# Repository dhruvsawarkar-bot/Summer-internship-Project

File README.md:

Analog Front-End PCB Design for Cyclic Voltammetry.
This project focuses on the design and development of an Analog Front-End current sensing circuit created for a Cyclic Voltammetry system. Developed during a research internship at the Sixth Sense Lab, IISER Bhopal, this board detects tiny electrical currents generated during chemical reactions and converts them into clear, measurable voltage signals for detailed analysis.  

Overview & Key FeaturesCore Function: 
1. Converts microampere-level currents produced during electrochemical reactions into readable voltage levels.
2. Amplifier Architecture: Utilizes an operational amplifier connected in a current-to-voltage conversion layout to ensure precise detection.
3. System Integration: Designed specifically to support three-electrode electrochemical testing setups for high-accuracy readings.
4. Hardware Connection: Uses simple pin header connectors for input signal lines, board power supply, and output measurement lines.
5. Board Layout: Optimized PCB layout designed in KiCad, featuring dedicated ground copper fills to block unwanted electrical noise and interference.

Bill of Materials Summary:
1. Operational Amplifier: Operational amplifier IC used as the core processing component.
2. Feedback Resistor: High-precision resistor that controls how much the input current is scaled into output voltage.
3. Connectors: Two-pin headers used to easily hook up input signals, power lines, and output connections.

Testing & Design Verification
Computer Simulation: Simulated using circuit software to ensure the board responds smoothly across the entire target current range before physical manufacturing.  
Design Rule Checks: Layout verified within KiCad to ensure trace widths and component clearances meet standard manufacturing requirements.  
Manufacturing Ready: Generated full production files (Gerber and drill files) ready for double-layer board fabrication.

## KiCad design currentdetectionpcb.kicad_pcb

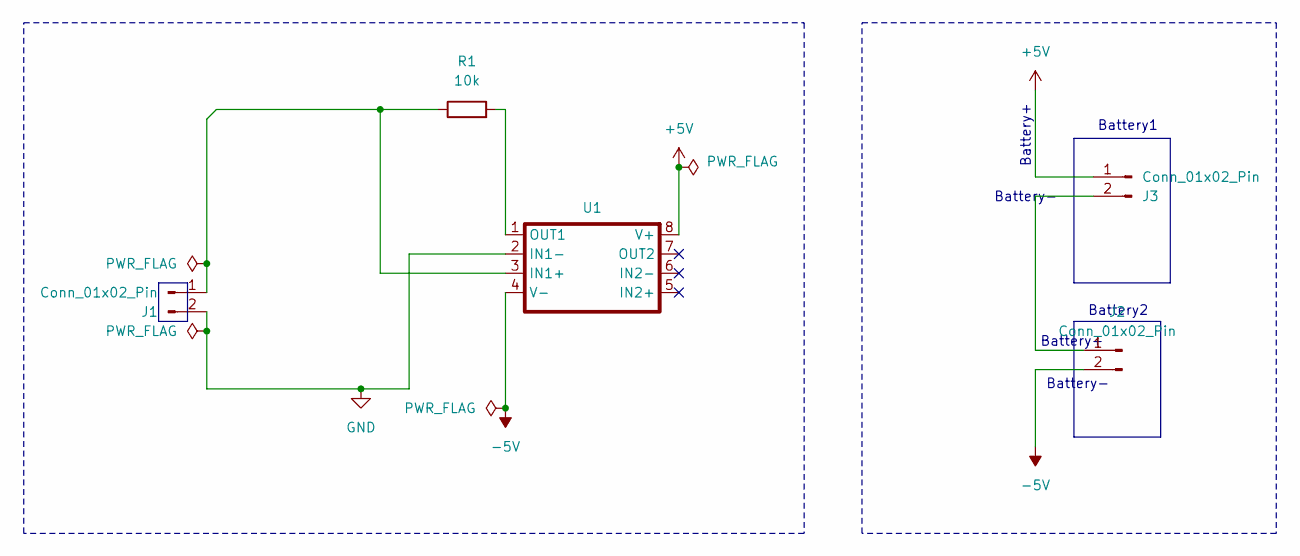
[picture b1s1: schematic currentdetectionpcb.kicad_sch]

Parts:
J1, J2, J3: Conn_01x02_Pin; PinHeader_1x02_P2.54mm_Vertical
R1: 10k; R_0805_2012Metric
U1: DIP-8_W7.62mm

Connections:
+5V: J3.1, U1.8 (V+)
-5V: J2.2, U1.4 (V-)
GND: J1.2, U1.2 (IN1-)
unnamed: J1.1, R1.1, U1.3 (IN1+)
unnamed: J2.1, J3.2
unnamed: R1.2, U1.1 (OUT1)

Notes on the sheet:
Battery+
Battery2
Battery1
Battery-

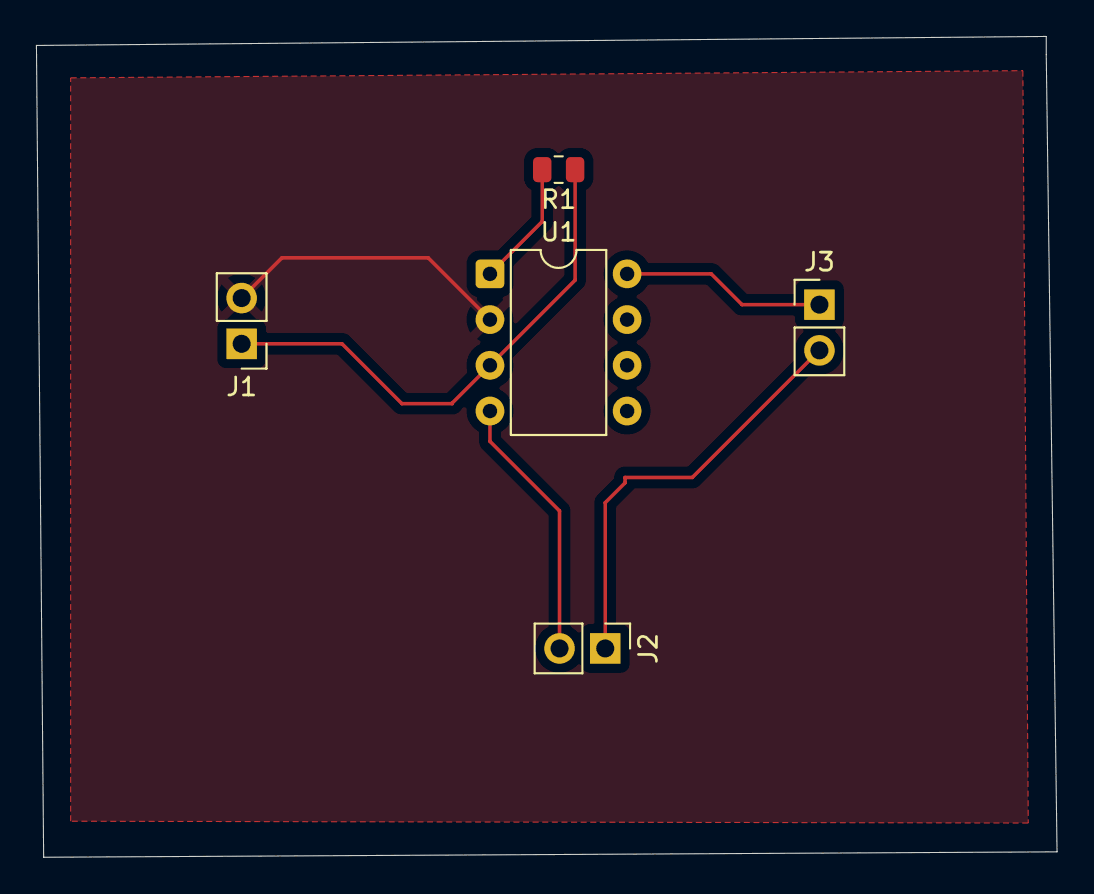
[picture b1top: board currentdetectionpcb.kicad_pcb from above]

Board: 2 copper layers, 56.7 x 45.6 mm, 5 parts (0 on the bottom side), 6 nets.
